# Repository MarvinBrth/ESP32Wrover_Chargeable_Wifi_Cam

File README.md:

# ESP32Wrover_Chargeable_Wifi_Cam
<div align="left">
- Created with KiCad
  
- Voltage regulator: Converts 5V to 3.3V for the microcontroller (MCU) and other voltage regulators for the camera
  
- MCU: ESP32-WROVER-E N8R8
  
- USB-C: For programming the microcontroller and charging the batteries
  
- Camera connection: For the 2MP OV2640 camera
  
- Automatic programming circuit: Allows programming without manual reset.
  
-  2 x 18560 Akkus

Schematic:

Layout:

3D-Model:

Fusion 360:

Real life:

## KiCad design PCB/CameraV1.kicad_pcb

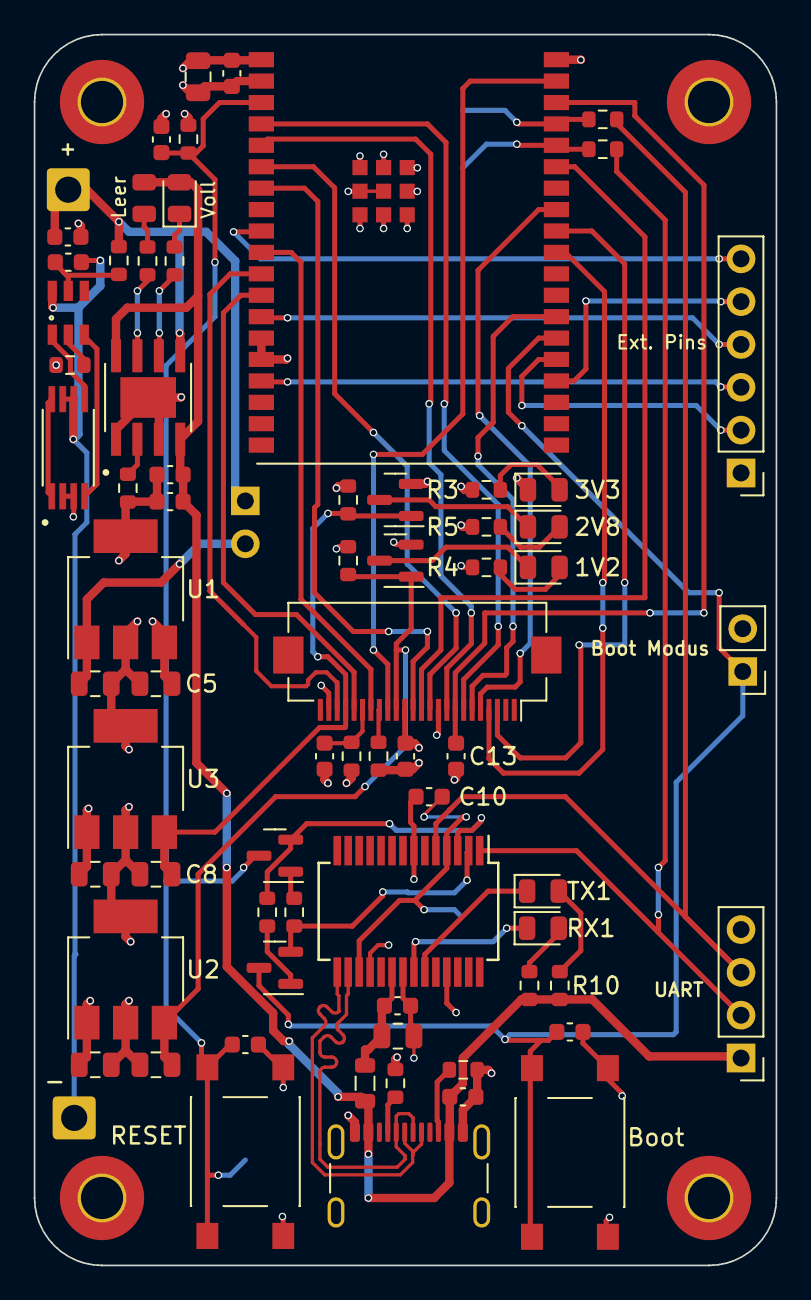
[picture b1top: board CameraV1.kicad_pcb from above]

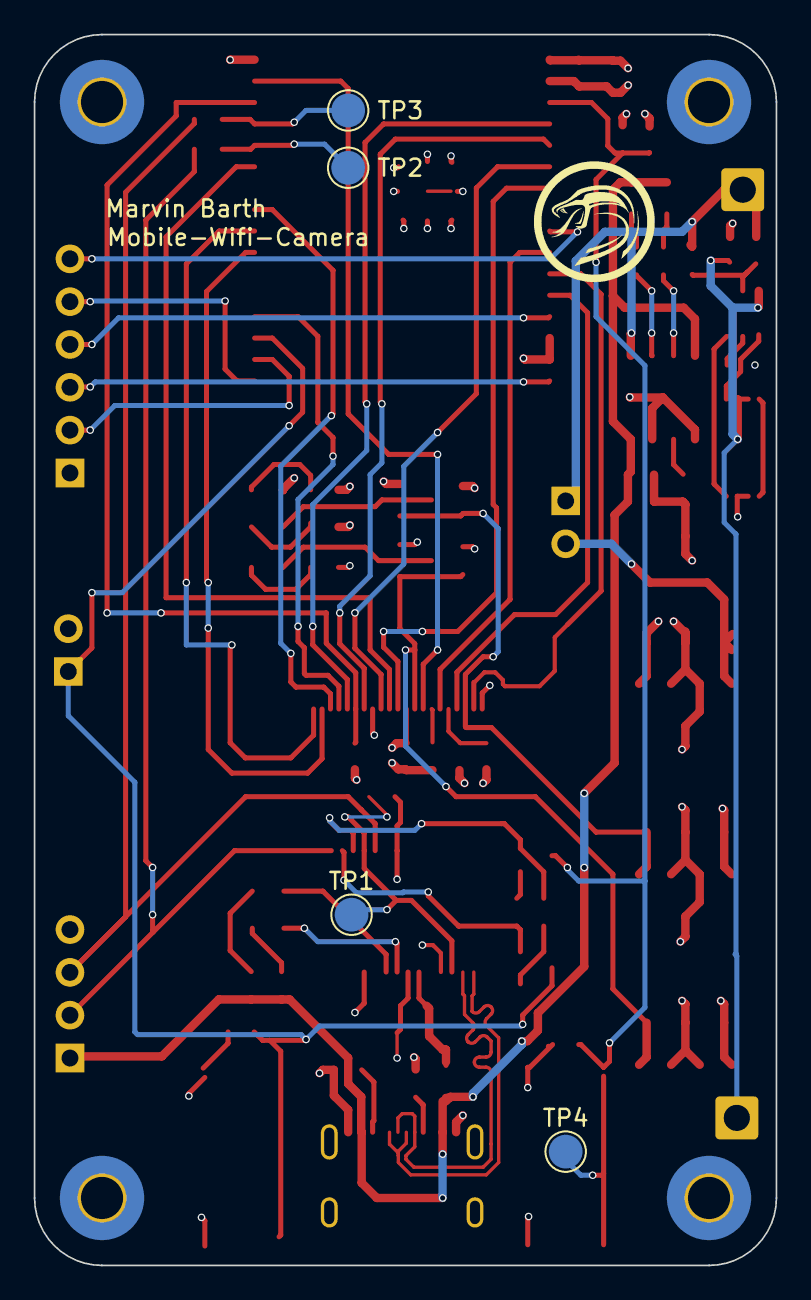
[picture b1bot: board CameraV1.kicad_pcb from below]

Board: 4 copper layers, 44.0 x 73.0 mm, 81 parts (4 on the bottom side), 63 nets.

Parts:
1V2, 2V8, 3V3: Blue; D_0805_2012Metric
+: 10uF; C_0603_1608Metric
-: Bat-; SolderWire-0.75sqmm_1x01_D1.25mm_OD2.3mm
Boot: SW_Push; SW_Push_1P1T_NO_6x6mm_H9.5mm
Boot Modus: Conn_01x02; PinHeader_1x02_P2.54mm_Vertical
C1, C2, C3, C5, C6, C8: 1uF; C_0805_2012Metric
C4: 10nF; C_0603_1608Metric
C7: 4.7uF; C_0805_2012Metric
C9, C10, C12, C14, C17, C18, C19, C20, C23: 100nF; C_0603_1608Metric
C11: 1uF; C_0603_1608Metric
C13: 15pF; C_0603_1608Metric
C15: 22uF; C_0805_2012Metric
C16: 22uF; C_0603_1608Metric
Ext. Pins: Conn_01x06; PinHeader_1x06_P2.54mm_Vertical
FB1: 1k; L_0805_2012Metric
H1, H2, H3, H4: MountingHole_Pad; MountingHole_2.5mm_Pad_TopBottom
H5: Bat+; SolderWire-0.75sqmm_1x01_D1.25mm_OD2.3mm
J1: USB_C_Receptacle_USB2.0; USB_C_Receptacle_GCT_USB4105-xx-A_16P_TopMnt_Horizontal
J4: Conn_01x24; Hirose_FH12-24S-0.5SH_1x24-1MP_P0.50mm_Horizontal
J6: Conn_01x02; PinHeader_1x02_P2.54mm_Vertical
Leer: D7; D_0805_2012Metric
Q1, Q2, Q4, Q5: BSS138; SOT-23
Q3: FS8205A; SOP65P640X120-8N
R1, R2: 5k1R; R_0603_1608Metric
R3, R4, R5, R10, R11, R13: 1kR; R_0603_1608Metric
R6, R7, R12, R16, R21: 10kR; R_0603_1608Metric
R8, R9: 0R; R_0603_1608Metric
R14, R15, R19: 1k; R_0603_1608Metric
R17: 1.2kR; R_0603_1608Metric
R18: 4k7R; R_0603_1608Metric
R20: 100R; R_0603_1608Metric
RESET: SW_Push; SW_Push_1P1T_NO_6x6mm_H9.5mm
RX1: Blue; D_0805_2012Metric
TP1, TP2, TP3, TP4: TestPoint_Probe; TestPoint_Pad_D2.0mm
TX1: Blue; D_0805_2012Metric
U1: MCP1703Ax-330xxDB; SOT-223-3_TabPin2
U2: MCP1703Ax-120xxDB; SOT-223-3_TabPin2
U3: MCP1703Ax-280xxDB; SOT-223-3_TabPin2
U4: FT232RL; SSOP-28_5.3x10.2mm_P0.65mm
U5: ESP32-WROVER-E-N8R8
U6: TP4056; DW01 SOP127P600X175-9N
U7: DW01A; SOT23-6
UART: Conn_01x04; PinHeader_1x04_P2.54mm_Vertical
Voll: D6; D_0805_2012Metric

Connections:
+1V2: C6.1, J4.15, Q1.1 (G), R6.2, U2.3 (VO)
+2V8: C8.1, J4.21, Q2.1 (G), R7.2, U3.3 (VO)
+3V3: C1.1, C3.1, C5.1, C12.2, C14.1, C15.1, Ext. Pins.1, J4.14, R3.1, R4.1, R5.1, R12.1, R18.2, U1.3 (VO), U2.1 (VI), U3.1 (VI), U5.2 (3V3)
/Boot Option: Boot.1, Boot Modus.1, C23.1, Q5.3 (D), U5.25 (IO0)
/CAM_RST: C19.1, J4.19, R18.1
/DTR: Q5.2 (S), R16.1, U4.2 (DTR)
/ESP_RST: C11.1, C18.1, Q4.3 (D), R12.2, RESET.1, TP4.1, U5.3 (EN)
/EXT_IO2: Ext. Pins.2, U5.24 (IO2)
/EXT_IO13: Ext. Pins.3, U5.16 (IO13)
/EXT_IO14: Ext. Pins.4, U5.13 (IO14)
/EXT_IO15: Ext. Pins.5, U5.23 (IO15)
/EXT_IO33: Ext. Pins.6, U5.9 (IO33)
/HREF: J4.16, U5.37 (IO23)
/OUT+: C2.1, J6.2, U1.1 (VI)
/PCLK: C13.2, J4.8, U5.36 (IO22)
/RTS: Q4.2 (S), R21.1, U4.3 (RTS)
/RX_ESP: R8.2, TP2.1, U5.34 (RXD0)
/RX_FT232: R9.1, U4.5 (RXD), UART.3
/RX_LED: RX1.1 (K), U4.22 (CBUS1)
/SIOC: J4.20, U5.12 (IO27)
/SIOD: J4.22, U5.11 (IO26)
/TX_ESP: R9.2, TP3.1, U5.35 (TXD0)
/TX_FT232: R8.1, U4.1 (TXD), UART.2
/TX_LED: TX1.1 (K), U4.23 (CBUS0)
/USB D+: J1.A6 (D+), J1.B6 (D+), U4.15 (USBD+)
/USB D-: J1.A7 (D-), J1.B7 (D-), U4.16 (USBD-)
/VBUS_5V: C4.1, C16.1, C17.1, FB1.1, J1.A4 (VBUS), J1.A9 (VBUS), J1.B4 (VBUS), J1.B9 (VBUS), Leer.2 (A), R10.2, R11.2, U6.4 (VCC), U6.8 (CE), UART.1, Voll.2 (A)
/VSYNC: J4.18, U5.10 (IO25)
/XCLK: J4.12, U5.33 (IO21)
/Y2: J4.6, U5.26 (IO4)
/Y3: J4.4, U5.29 (IO5)
/Y4: J4.3, U5.30 (IO18)
/Y5: J4.5, U5.31 (IO19)
/Y6: J4.7, U5.4 (SENSOR_VP)
/Y7: J4.9, U5.5 (SENSOR_VN)
/Y8: J4.11, U5.6 (IO34)
/Y9: J4.13, U5.7 (IO35)
GND: 3V3.1 (K), +.2, Boot.2, Boot Modus.2, C1.2, C2.2, C3.2, C4.2, C5.2, C6.2, C7.2, C8.2, C9.2, C10.2, C11.2, C12.1, C13.1, C14.2, C15.2, C16.2, C17.2, C18.2, C19.2, C23.2, H1.1, H2.1, H3.1, H4.1, J1.A1 (GND), J1.A12 (GND), J1.B1 (GND), J1.B12 (GND), J1.S1 (SHIELD), J4.10, J4.23, Q1.2 (S), Q2.2 (S), Q3.2, Q3.3, R1.2, R2.2, R6.1, R7.1, R13.1, R17.2, R19.2, RESET.2, U1.2 (GND), U2.2 (GND), U3.2 (GND), U4.7 (GND), U4.18 (GND), U4.21 (GND), U4.25 (AGND), U5.1 (GND), U5.14 (IO12), U5.15 (GND), U5.38 (GND), U5.39_1 (EXP), U5.39_2 (EXP), U5.39_3 (EXP), U5.39_4 (EXP), U5.39_5 (EXP), U5.39_6 (EXP), U5.39_7 (EXP), U5.39_8 (EXP), U5.39_9 (EXP), U6.1 (TEMP), U6.3 (GND), U6.9 (EP), UART.4
unnamed: 1V2.2 (A), R4.2
unnamed: 1V2.1 (K), Q1.3 (D)
unnamed: 2V8.2 (A), R5.2
unnamed: 2V8.1 (K), Q2.3 (D)
unnamed: 3V3.2 (A), R3.2
unnamed: J1.A5 (CC1), R2.1
unnamed: J1.B5 (CC2), R1.1
unnamed: J4.17, R13.2
unnamed: +.1, H5.1, J6.1, R20.2, U6.5 (BAT)
unnamed: Leer.1 (K), R15.2
unnamed: Q4.1 (G), R16.2
unnamed: Q5.1 (G), R21.2
unnamed: R11.1, RX1.2 (A)
unnamed: R10.1, TX1.2 (A)
unnamed: C10.1, TP1.1, U4.4 (VCCIO), U4.17 (3V3OUT)
unnamed: C7.1, C9.1, FB1.2, U4.20 (VCC)
unnamed: R17.1, U6.2 (PROG)
unnamed: R15.1, U6.7 (~CHRG)
unnamed: R14.1, U6.6 (~STDBY)
unnamed: R19.1, U7.2 (CS)
unnamed: -.1, C20.2, Q3.6, Q3.7, U7.6 (GND)
unnamed: Q3.4, U7.3 (OC)
unnamed: Q3.5, U7.1 (OD)
unnamed: C20.1, R20.1, U7.5 (VCC)
unnamed: R14.2, Voll.1 (K)

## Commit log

2024-08-07 Add files via upload
    Erstellt mit KiCad.
    Spannungsregler: Wandelt 5V auf 3.3V für den Mikrocontroller (MCU) und weitere Spannungsregler für die Kamera.
    MCU: ESP32-WROVER-E N8R8.
    USB-C: Für die Programmierung des Mikrocontrollers und das Laden der Akkus.
    Kameraanschluss: Für die 2MP OV2640 Kamera.
    Automatische Programmierungsschaltung: Erlaubt Programmierung ohne manuellen Reset.
2024-08-07 Create PCB
2024-08-07 Create keep
